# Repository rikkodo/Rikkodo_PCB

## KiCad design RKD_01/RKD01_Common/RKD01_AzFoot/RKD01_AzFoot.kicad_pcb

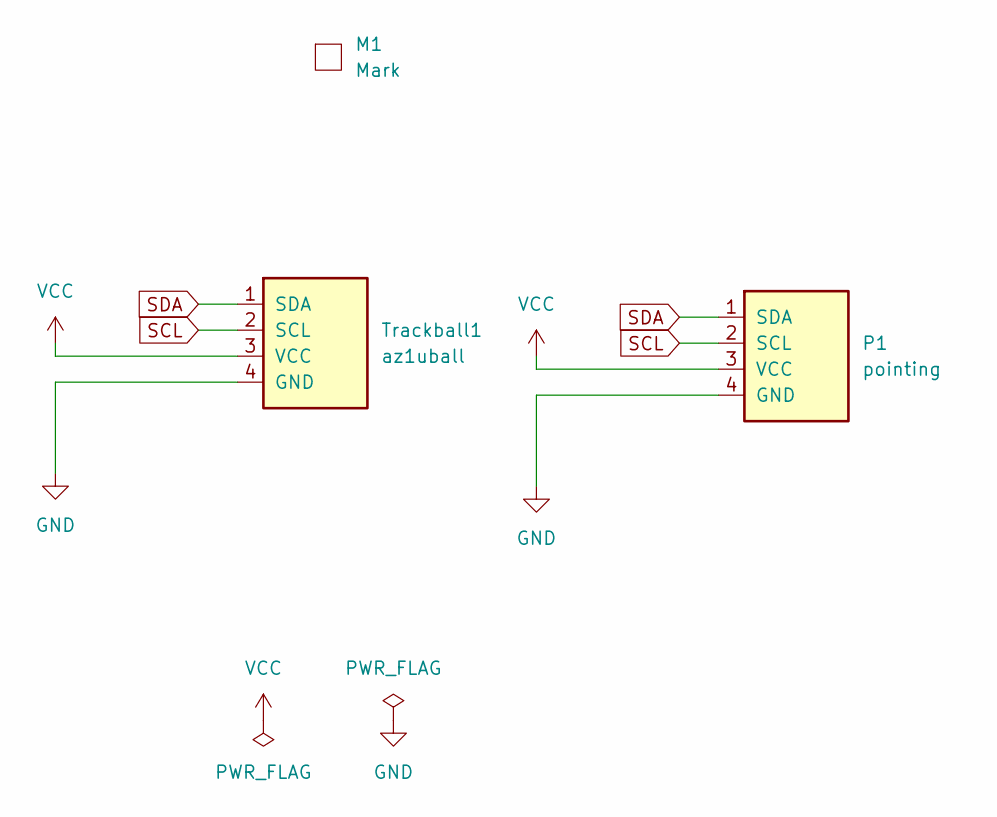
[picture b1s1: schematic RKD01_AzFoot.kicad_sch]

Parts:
M1: Mark; rkd_Point_Cut
P1: pointing; OLED
Trackball1: az1uball; AZ1UBALL

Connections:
GND: P1.4 (GND), Trackball1.4 (GND)
SCL: P1.2 (SCL), Trackball1.2 (SCL)
SDA: P1.1 (SDA), Trackball1.1 (SDA)
VCC: P1.3 (VCC), Trackball1.3 (VCC)

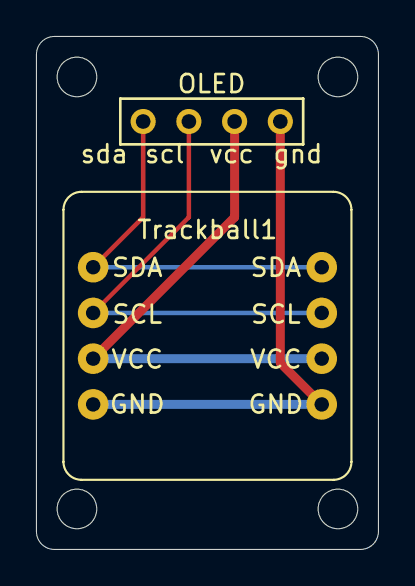
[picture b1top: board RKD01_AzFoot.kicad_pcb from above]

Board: 2 copper layers, 19.0 x 28.5 mm, 3 parts (0 on the bottom side), 4 nets.

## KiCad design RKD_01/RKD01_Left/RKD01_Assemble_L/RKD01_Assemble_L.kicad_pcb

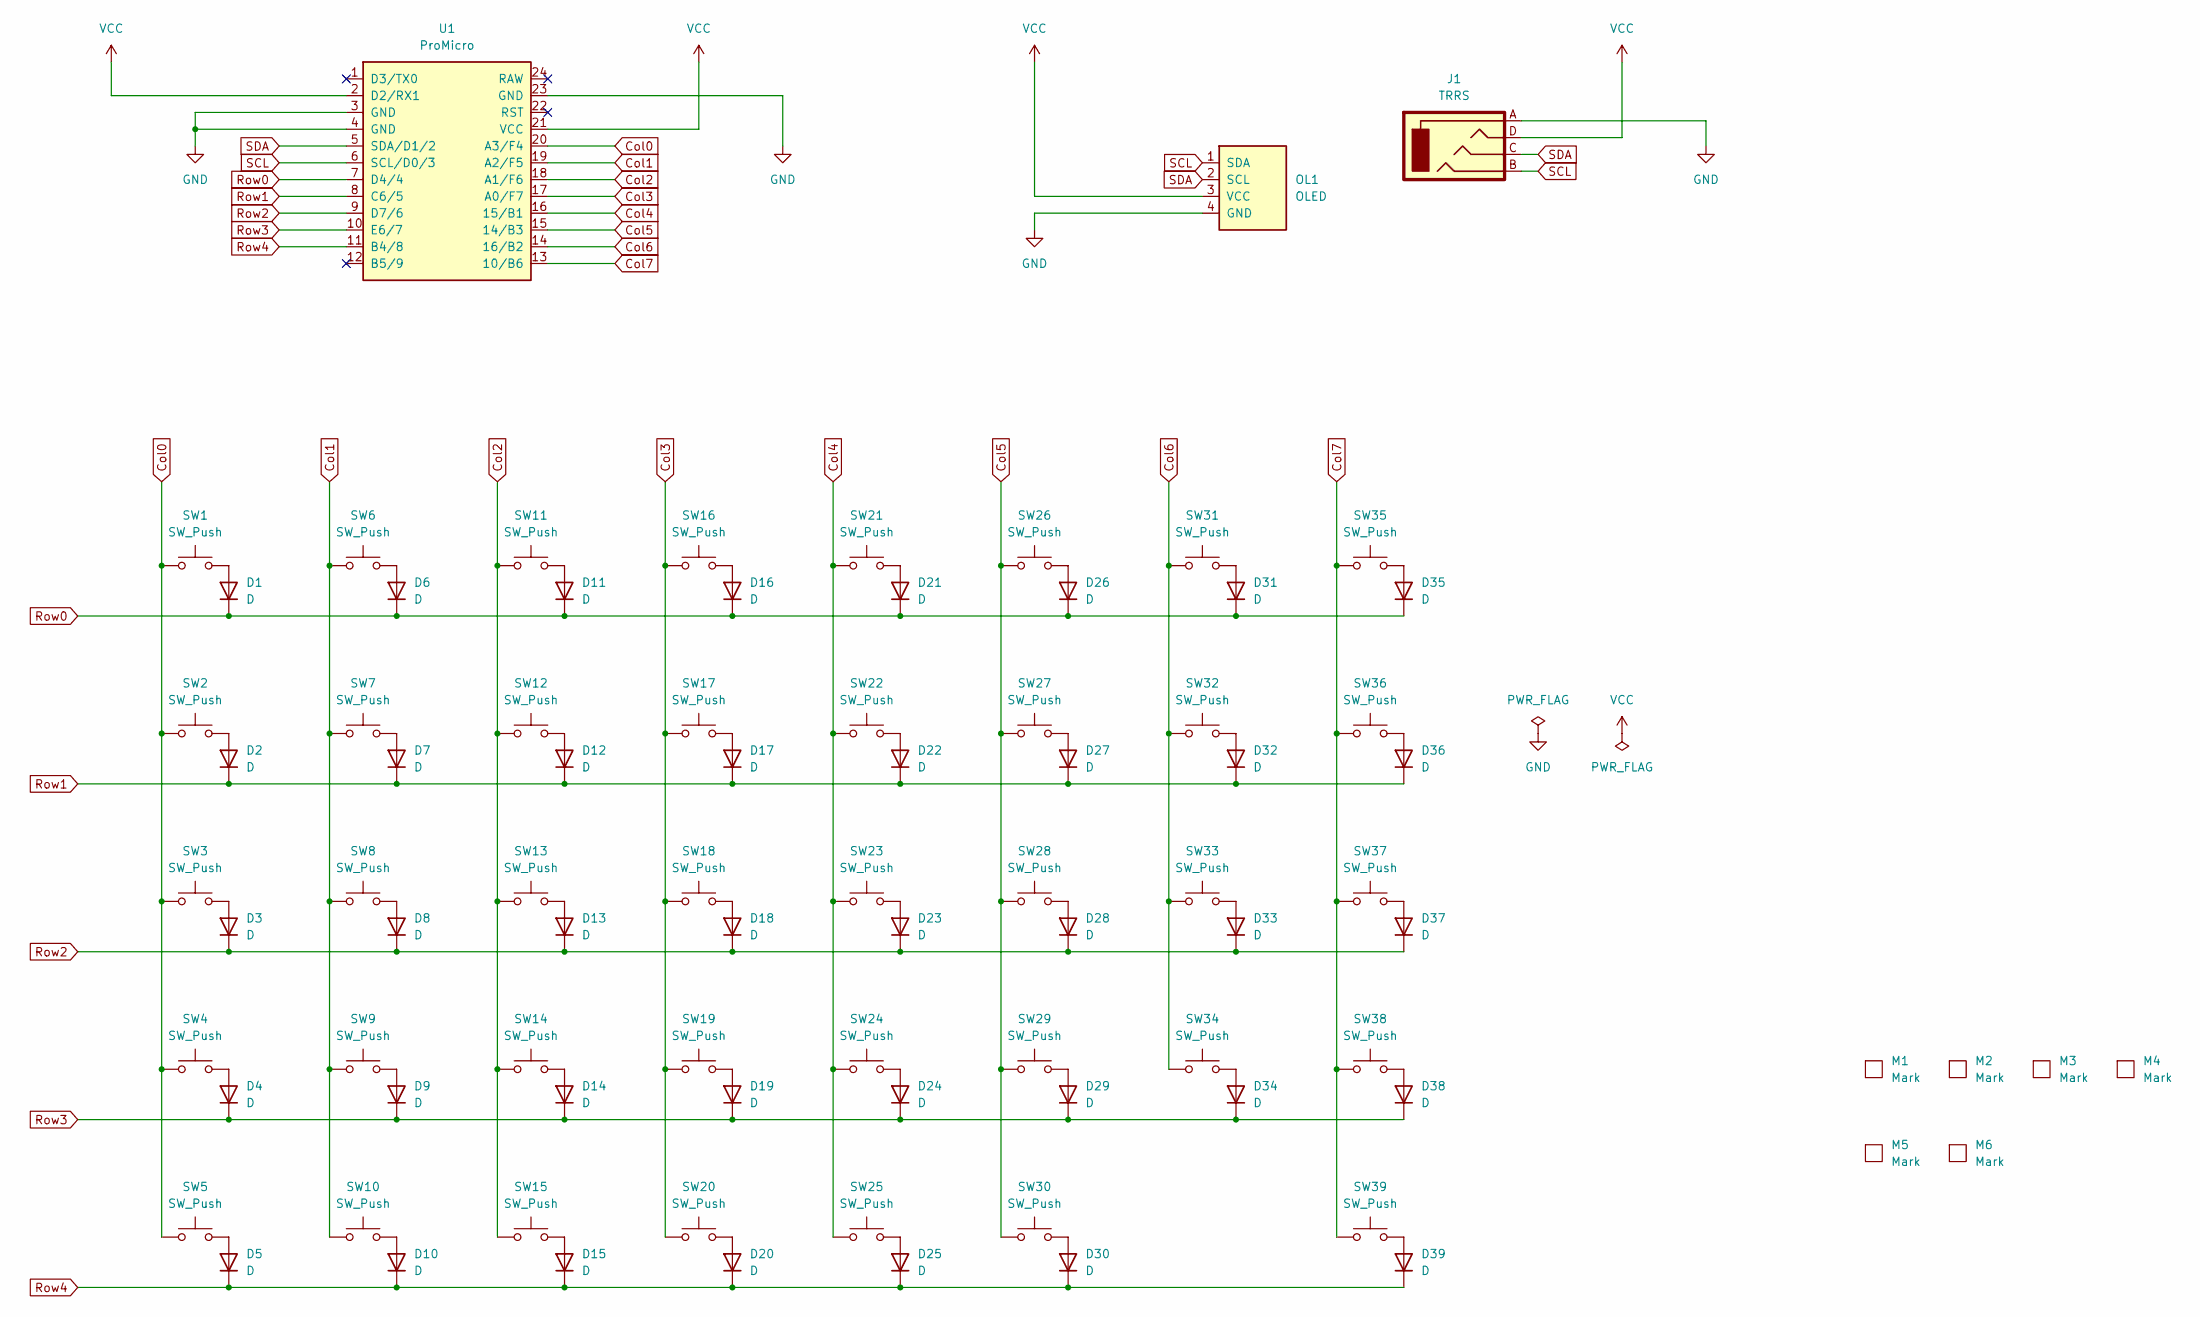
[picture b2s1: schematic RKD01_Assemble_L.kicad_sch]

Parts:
D1, D2, D3, D4, D5, D6, D7, D8, D9, D10, D11, D12, D13, D14, D15, D16, D17, D18, D19, D20, D21, D22, D23, D24, D25, D26, D27, D28, D29, D30, D31, D32, D33, D34, D35, D36, D37, D38, D39: D; Diode_TH_SMD
J1: TRRS; TRRS_PJ-320A
M1, M2, M3, M4: Mark; m2_Spacer_Hole_hex
M5, M6: Mark; m2_Screw_Hole
OL1: OLED; OLED_center_module
SW1, SW2, SW3, SW4, SW5, SW6, SW7, SW8, SW10, SW11, SW12, SW13, SW14, SW15, SW16, SW17, SW18, SW19, SW20, SW21, SW22, SW23, SW24, SW25, SW26, SW27, SW28, SW29, SW31, SW32, SW33, SW34, SW35, SW36, SW37, SW38, SW39: SW_Push; rkd_Choc_v2_Hotswap_1u
SW9, SW30: SW_Push; rkd_Choc_v2_Hotswap_2u
U1: ProMicro; ProMicro_r

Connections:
Col0: SW1.2, SW2.2, SW3.2, SW4.2, SW5.2, U1.20 (A3/F4)
Col1: SW6.2, SW7.2, SW8.2, SW9.2, SW10.2, U1.19 (A2/F5)
Col2: SW11.2, SW12.2, SW13.2, SW14.2, SW15.2, U1.18 (A1/F6)
Col3: SW16.2, SW17.2, SW18.2, SW19.2, SW20.2, U1.17 (A0/F7)
Col4: SW21.2, SW22.2, SW23.2, SW24.2, SW25.2, U1.16 (15/B1)
Col5: SW26.2, SW27.2, SW28.2, SW29.2, SW30.2, U1.15 (14/B3)
Col6: SW31.2, SW32.2, SW33.2, SW34.2, U1.14 (16/B2)
Col7: SW35.2, SW36.2, SW37.2, SW38.2, SW39.2, U1.13 (10/B6)
GND: J1.A, OL1.4 (GND), U1.3 (GND), U1.4 (GND), U1.23 (GND)
unnamed: D1.2 (A), SW1.1
unnamed: D2.2 (A), SW2.1
unnamed: D3.2 (A), SW3.1
unnamed: D4.2 (A), SW4.1
unnamed: D5.2 (A), SW5.1
unnamed: D6.2 (A), SW6.1
unnamed: D7.2 (A), SW7.1
unnamed: D8.2 (A), SW8.1
unnamed: D9.2 (A), SW9.1
unnamed: D10.2 (A), SW10.1
unnamed: D11.2 (A), SW11.1
unnamed: D12.2 (A), SW12.1
unnamed: D13.2 (A), SW13.1
unnamed: D14.2 (A), SW14.1
unnamed: D15.2 (A), SW15.1
unnamed: D16.2 (A), SW16.1
unnamed: D17.2 (A), SW17.1
unnamed: D18.2 (A), SW18.1
unnamed: D19.2 (A), SW19.1
unnamed: D20.2 (A), SW20.1
unnamed: D21.2 (A), SW21.1
unnamed: D22.2 (A), SW22.1
unnamed: D23.2 (A), SW23.1
unnamed: D24.2 (A), SW24.1
unnamed: D25.2 (A), SW25.1
unnamed: D26.2 (A), SW26.1
unnamed: D27.2 (A), SW27.1
unnamed: D28.2 (A), SW28.1
unnamed: D29.2 (A), SW29.1
unnamed: D30.2 (A), SW30.1
unnamed: D31.2 (A), SW31.1
unnamed: D32.2 (A), SW32.1
unnamed: D33.2 (A), SW33.1
unnamed: D34.2 (A), SW34.1
unnamed: D35.2 (A), SW35.1
unnamed: D36.2 (A), SW36.1
unnamed: D37.2 (A), SW37.1
unnamed: D38.2 (A), SW38.1
unnamed: D39.2 (A), SW39.1
Row0: D1.1 (K), D6.1 (K), D11.1 (K), D16.1 (K), D21.1 (K), D26.1 (K), D31.1 (K), D35.1 (K), U1.7 (D4/4)
Row1: D2.1 (K), D7.1 (K), D12.1 (K), D17.1 (K), D22.1 (K), D27.1 (K), D32.1 (K), D36.1 (K), U1.8 (C6/5)
Row2: D3.1 (K), D8.1 (K), D13.1 (K), D18.1 (K), D23.1 (K), D28.1 (K), D33.1 (K), D37.1 (K), U1.9 (D7/6)
Row3: D4.1 (K), D9.1 (K), D14.1 (K), D19.1 (K), D24.1 (K), D29.1 (K), D34.1 (K), D38.1 (K), U1.10 (E6/7)
Row4: D5.1 (K), D10.1 (K), D15.1 (K), D20.1 (K), D25.1 (K), D30.1 (K), D39.1 (K), U1.11 (B4/8)
SCL: J1.B, OL1.1 (SDA), U1.6 (SCL/D0/3)
SDA: J1.C, OL1.2 (SCL), U1.5 (SDA/D1/2)
VCC: J1.D, OL1.3 (VCC), U1.2 (D2/RX1), U1.21 (VCC)

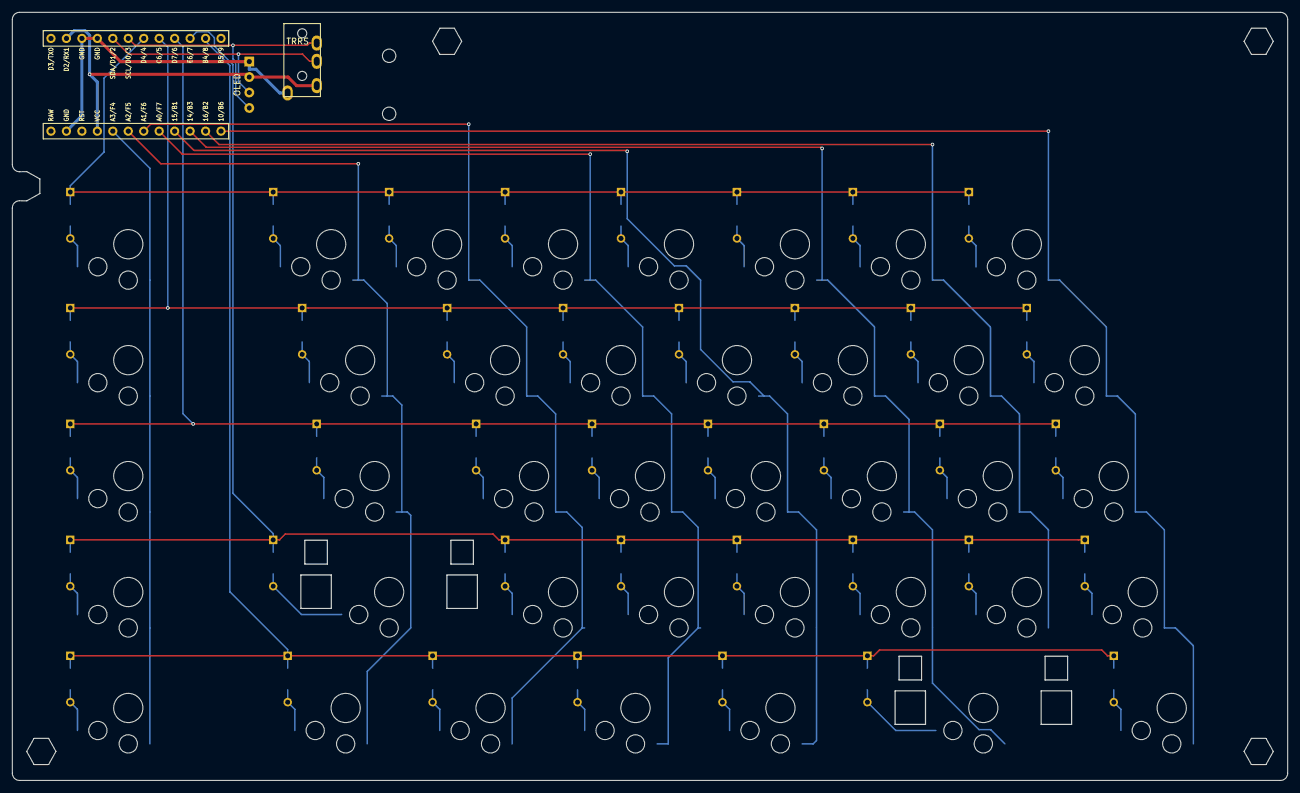
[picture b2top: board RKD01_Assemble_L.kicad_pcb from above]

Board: 2 copper layers, 209.6 x 126.2 mm, 87 parts (0 on the bottom side), 56 nets.
